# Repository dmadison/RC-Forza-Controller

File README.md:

# RC Controller for Forza
This project converts a DUMBORC x4 remote control for an RC car into a controller for [Forza Horizon 4](https://forzamotorsport.net/en-us/games/fh4). A USB-capable microcontroller reads the receiver's PWM pulses and translates the signals into Xbox controller (XInput) inputs for the game.

For more information, check out the article on [PartsNotIncluded.com](https://www.partsnotincluded.com/modifying-an-rc-controller-to-play-forza-horizon).

## Dependencies
The microcontroller code has several dependencies:

* [ArduinoXInput](https://github.com/dmadison/ArduinoXInput) [(v1.2.3)](https://github.com/dmadison/ArduinoXInput/releases/tag/v1.2.3)
* [ServoInput](https://github.com/dmadison/ServoInput) [(v1.0.0)](https://github.com/dmadison/ServoInput/releases/tag/v1.0.0)
* [ArduinoXInput AVR Core](https://github.com/dmadison/ArduinoXInput_AVR) [(v1.0.1)](https://github.com/dmadison/ArduinoXInput_AVR/releases/tag/v1.0.1)

I've linked to the specific releases that work with this code. Note that other versions may not be compatible.

This project was compiled using version 1.8.12 of the Arduino IDE. Microcontrollers other than the ATmega32U4 may be compatible but have not been tested.

## License
This project is licensed under the terms of the [GNU General Public License](https://www.gnu.org/licenses/gpl-3.0.en.html), either version 3 of the License, or (at your option) any later version.

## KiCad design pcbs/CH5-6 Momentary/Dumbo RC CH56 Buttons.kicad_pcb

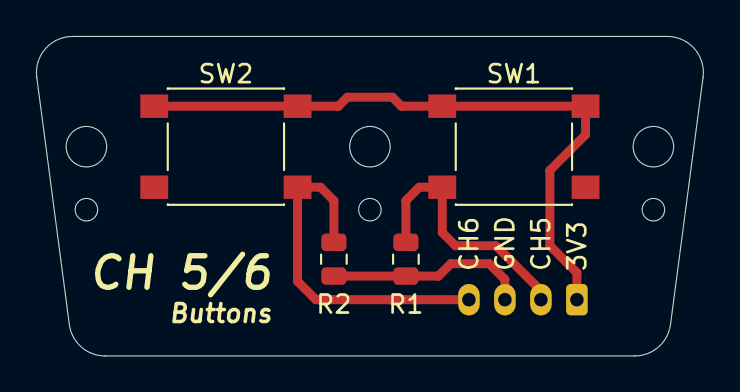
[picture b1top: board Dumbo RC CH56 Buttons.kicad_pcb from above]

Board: 2 copper layers, 37.1 x 17.8 mm, 11 parts (1 on the bottom side), 4 nets.

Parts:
H1, H2, H3: MountingHole; MountingHole_2.25mm
H4, H5, H6: AlignmentHole; AlignmentHole_1.25mm
J1: Conn_01x04; JST_PH_B4B-PH-K_1x04_P2.00mm_Vertical
R1, R2: 10k; R_0805_2012Metric
SW1, SW2: SW_Push; SW_SPST_PTS645

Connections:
/3V3: J1.1, SW1.1, SW2.1
/CH5: J1.2, R1.1, SW1.2
/CH6: J1.4, R2.1, SW2.2
GND: J1.3, R1.2, R2.2

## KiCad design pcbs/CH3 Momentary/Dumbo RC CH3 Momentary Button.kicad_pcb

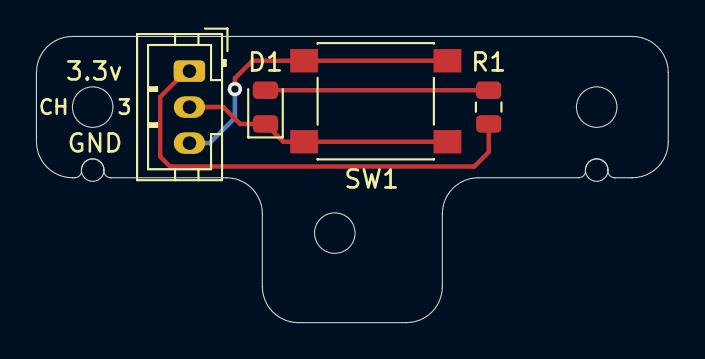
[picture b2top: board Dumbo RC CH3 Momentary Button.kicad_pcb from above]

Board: 2 copper layers, 35.1 x 15.9 mm, 9 parts (0 on the bottom side), 4 nets.

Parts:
D1: LED; LED_0805_2012Metric
H1, H2, H3: MountingHole; MountingHole_2.25mm
H4, H5: AlignmentHole; AlignmentHole_1.25mm
J1: Conn_01x03; JST_PH_B3B-PH-K_1x03_P2.00mm_Vertical
R1: 330 Ω; R_0805_2012Metric
SW1: SW_Push; SW_SPST_PTS645

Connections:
/3V3: J1.1, R1.2
/CH3: D1.1, J1.2, SW1.2
/GND: J1.3, SW1.1
unnamed: D1.2, R1.1

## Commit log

2020-11-10 Create LICENSE
